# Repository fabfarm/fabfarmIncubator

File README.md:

# Fabfarm Egg Incubator

This is the code repository for the Fabfarm Egg Incubator, a project for controlling and monitoring the temperature, humidity, and egg tray position inside an egg incubator.

## Features

- Temperature control using a relay
- Humidity control using a vent servo
- Egg tray rotation using a tray servo
- Sensor data display on a TFT screen
- Web interface for configuration and data visualization
- Data logging to SPIFFS
- PID control for temperature and humidity

## Hardware Requirements

- ESP32 microcontroller
- BME280 temperature, humidity and pressure sensor
- Relay module for temperature control
- Servo motor for vent control (humidity)
- Servo motor for tray rotation
- TFT display (ILI9341 based)

## Software Dependencies

- Arduino IDE
- Adafruit BME280 library
- ESP32Servo library
- TFT_eSPI library
- ESPAsyncWebServer library
- WiFiManager library
- FS.h, SPIFFS.h, and SPI.h libraries (built-in)
- PID_v1 library

## Getting Started

1. Clone this repository to your local machine.
2. Open the project folder ./firmware using platformio.
3. Platformio will install the required libraries mentioned in the Software Dependencies section.
4. Connect the hardware components as described in the Hardware Requirements section.
5. Upload the code to the ESP32 microcontroller.
6. In first time connect to the "AutoConnectAP" Wi-Fi network and configure the Wi-Fi settings.
7. Access the web interface by navigating to the IP address displayed on the TFT screen.
8. Configure temperature, humidity, and servo settings using the web interface.
9. Monitor the incubator data on the web interface and TFT screen.

### React frontend

#### General Setup:

0. you must have node, npm or a comparable package manager installed. (node >18)
1. path to the `./firmware/client` folder
2. run `npm install` to locally install your dependencies for the project
3. add a `.env` file by copying the .env.example file and replacing the values with the IP produced by the chip when it is setting up. (This will most likely be a dynamic IP so it is important to check if this has changed with every setup.)

#### Developing

The react frontend lives as its own project in the `./firmware/client` folder.

We can host the development server

#### Building

In order to build the react frontend files you must have node and npm or a comparable package manager installed.

The frontend files are built, compressed and placed in the ESP32 filesystem.

To do this, path to `./firmware/client` and run `npm run build`.

After this you can flash the chip and it'll have the latest version of the frontend available to you.

## Functionality Overview

- The incubator monitors and controls temperature and humidity using a BME280 sensor and a relay and servo motor, respectively.
- The egg tray position is controlled by a servo motor, which rotates the tray at regular intervals.
- Sensor data is displayed on the TFT screen and logged to the ESP32's SPIFFS memory.
- A web interface is provided for configuring temperature, humidity, and servo settings, as well as for visualizing logged data.
- The system can be paused or resumed using the web interface.

## Contributing

Feel free to fork this repository and submit pull requests for bug fixes, improvements, or new features. Please ensure that your code follows the existing style and structure.

## License

This project is licensed under the MIT License. See the [LICENSE](LICENSE) file for more information.

## Acknowledgements

This project was written by Lucio.
The react frontend was built by @NoHara42

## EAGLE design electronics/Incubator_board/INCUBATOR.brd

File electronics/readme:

placeholder for electronics files

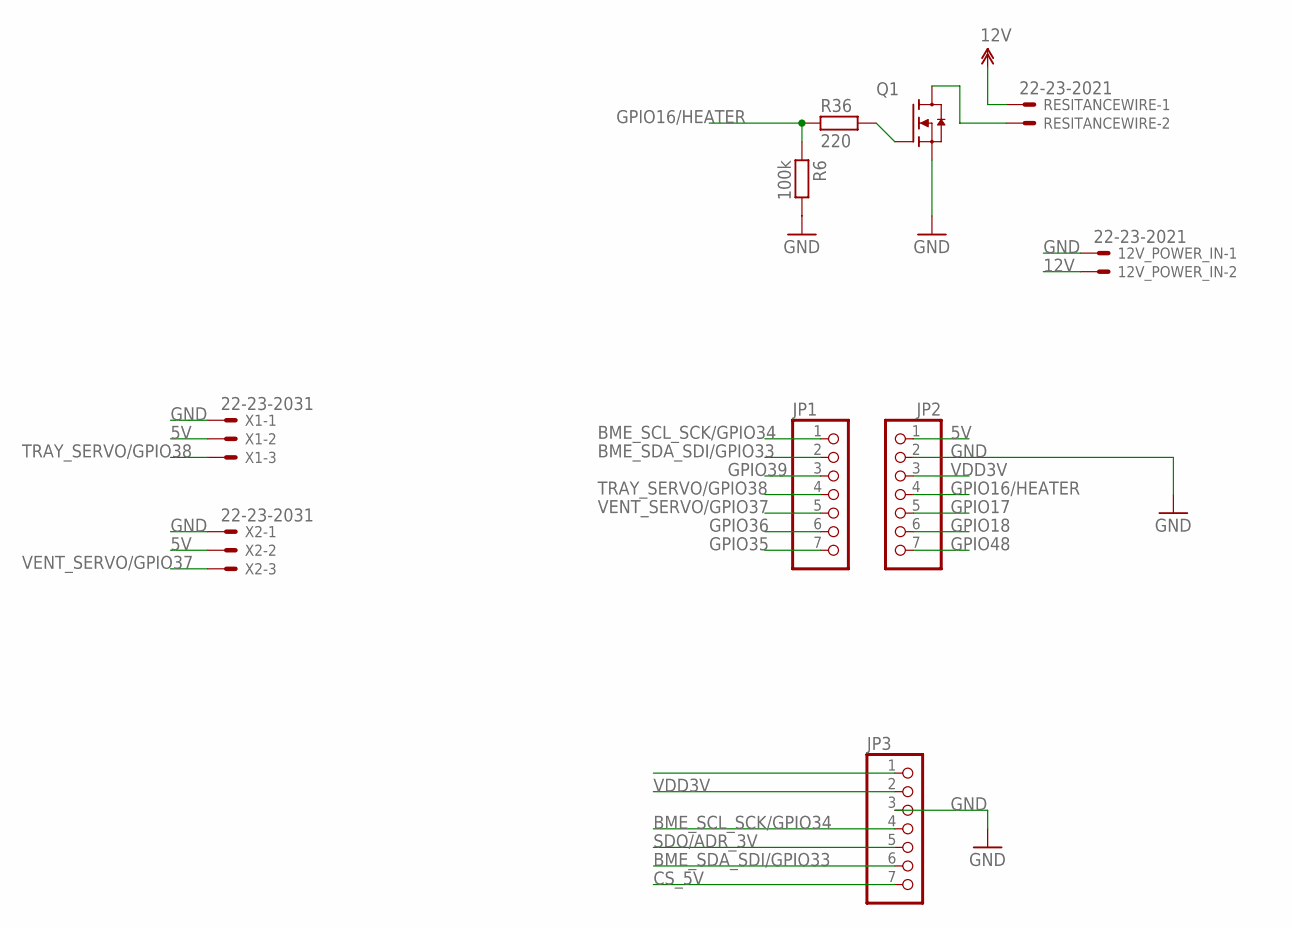
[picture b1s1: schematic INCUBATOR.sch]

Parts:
12V_POWER_IN: 22-23-2021
JP1, JP2: PINHD-1X7; 1X07
JP3: HEADER-1X770MIL; 1X07_ROUND_70
Q1: RFP30N06LE; TO92127P520H700-3
R6: 100k; RESC2012X70N
R36: 220; RESC2012X70N
RESITANCEWIRE: 22-23-2021
X1, X2: 22-23-2031

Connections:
5V: JP2.1, X1.2, X2.2
12V: 12V_POWER_IN.2, RESITANCEWIRE.1
BME_SCL_SCK/GPIO34: JP1.1, JP3.4
BME_SDA_SDI/GPIO33: JP1.2, JP3.6
CS_5V: JP3.7
GND: 12V_POWER_IN.1, JP2.2, JP3.3, Q1.S (SOURCE), R6.2, X1.1, X2.1
GPIO16/HEATER: JP2.4, R6.1, R36.1
GPIO17: JP2.5
GPIO18: JP2.6
GPIO35: JP1.7
GPIO36: JP1.6
GPIO39: JP1.3
GPIO48: JP2.7
HOTEND-GND: Q1.D (DRAIN), RESITANCEWIRE.2
unnamed: Q1.G (GATE), R36.2
SDO/ADR_3V: JP3.5
TRAY_SERVO/GPIO38: JP1.4, X1.3
VDD3V: JP2.3, JP3.2
VENT_SERVO/GPIO37: JP1.5, X2.3

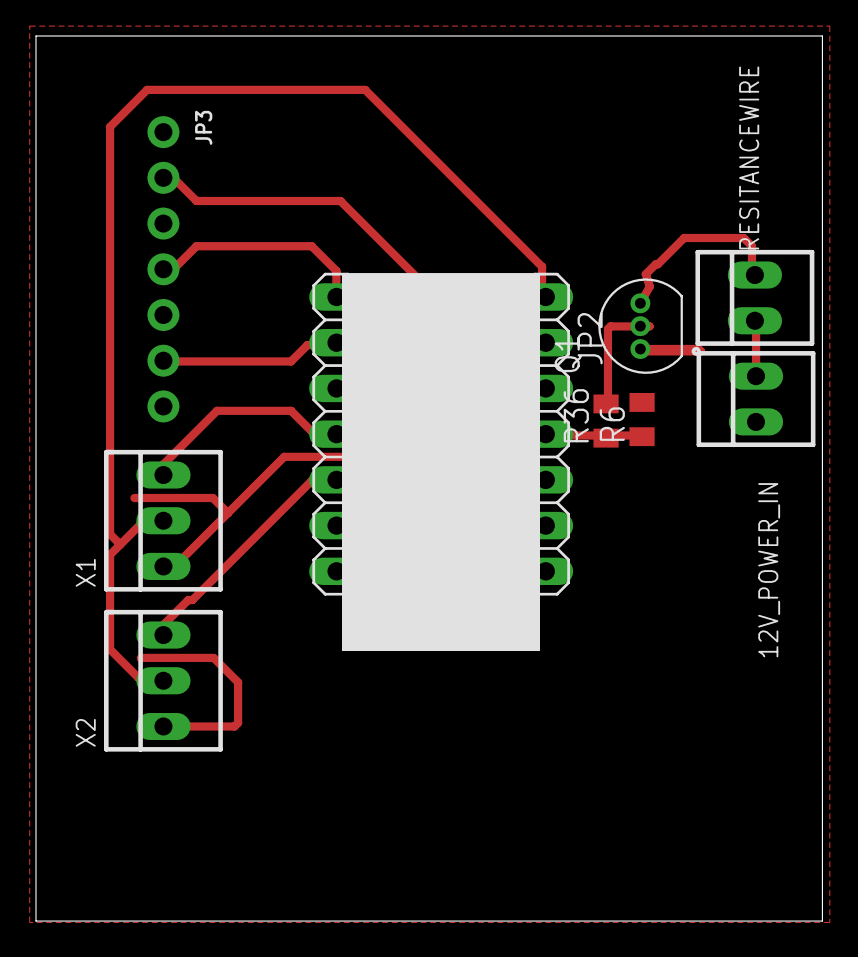
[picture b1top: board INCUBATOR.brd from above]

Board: 2 copper layers, 43.7 x 49.2 mm, 10 parts (0 on the bottom side), 11 nets.

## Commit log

2023-04-18 many changes to track
2023-04-19 added one decimal to temperatures
2023-04-21 improving layout
2023-04-24 added PID optimized code
2023-04-24 clean up
2023-04-24 many stuff
2023-04-24 bug fix
2023-04-25 new names for functions and variables
2023-04-30 Refactor: Remove hard-coded PID settings and move them to separate files Cleanup: Remove unnecessary files and improve PID configuration
2023-04-30 Reduce code size: Add ternary operator to function and implement it where necessary
2023-04-30 fix bug from last commit
2023-04-30 Refactoring code for improved readability and efficiency by reducing character count and simplifying logic
2023-04-30 fixed bug where the function where calling itself
2023-05-02 html now shows the current settings
2023-05-02 changes in html formating
2023-05-02 reducing code size
2023-05-03 cleanup
2023-05-03 changes in the readme
2023-05-04 simplified directory tree
2023-05-04 created a placeholder for the future electronics files and the cad files
2023-05-05 added notosans font
2023-05-05 moved Documentation folder to root
2023-05-05 added pcb
2023-05-08 add unix-friendly alternative shell script for development
2023-05-10 fix errors in unix alt flash script
2023-05-10 add comments for prereq steps
2023-05-10 changes in the board
2023-05-11 init preact project
2023-05-11 board updates
2023-05-11 add .clang-format file for unified formating
2023-05-11 restructure client folder
2023-05-11 removed PID deumbed down to a working version until sorted problems
2023-05-12 add .env to .gitignore
2023-05-12 temperature control without PID working added Elegant OTA
2023-05-12 gitignore additions
2023-05-15 add dependencies and fix comitted conflict markers
2023-05-15 fix tailwind config and add base styles
2023-05-15 add base template with mock data
2023-05-15 Refactor: Split code into distinct functionalities for better maintenance
    This commit divides the existing codebase into distinct and self-contained functionalities. This reorganization significantly improves the code's readability, maintainability, and potential for furth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
    No functionality has been added or removed in this commit; the focus was purely on restructuring the code for better maintenance.
2023-05-16 Refactor DisplayManager.cpp for better readability and maintenance
    This commit includes several improvements to the DisplayManager.cpp file:
    1. Extracted repeated code in updateTFTDisplay into a new function, updateLineIfChanged, to reduce code duplication and improve readability.
    2. Introduced a function, displayTargetValue, to handle displaying of target values, removing repeated code.
    3. Replaced magic numbers with named constants for better code clarity and ease of maintenance.
    4. Added comments for clarity.
    These changes should make the code easier to understand, modify, and maintain in the future.
2023-05-16 add dependencies and adapt scrips
2023-05-16 add env typing
2023-05-16 refactor app.tsx and add react-query
2023-05-16 add sidenav controls
2023-05-16 add build files
2023-05-16 extract endpoints to pure atoms
2023-05-16 fix misnaming
2023-05-18 remove whitespace
2023-05-18 adapt formatting config
2023-05-18 correct order of .sh script to stop error
2023-05-18 format and add readFile function to FileManager
2023-05-18 format main.cpp
2023-05-18 adapt package.json scripts and add build dep
2023-05-18 adapt build script
2023-05-18 decrease sampling speed via millis and seperate data to different .csv files
2023-05-18 Bump certifi from 2020.12.5 to 2022.12.7 in /firmware/lib/lvgl/docs
    Bumps [certifi](https://github.com/certifi/python-certifi) from 2020.12.5 to 2022.12.7.
    - [Commits](https://github.com/certifi/python-certifi/compare/2020.12.05...2022.12.07)
    ---
    updated-dependencies:
    - dependency-name: certifi
    dependency-type: direct:production
2023-05-18 Implement PID control for temperature and humidity
    - Added PID control functionality for both temperature and humidity
    - Declared necessary variables for PID control operation
    - Imported required libraries for PID control
    This implementation uses the PID Arduino library for controlling the temperature and humidity of a specific system. Each control loop has its corresponding input, output, setpoint, and tuning paramet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
2023-05-19 forgot some stuff for the PID
2023-05-19 added missing loadSettings parameters for the PID setings display.
2023-05-19 add ArduinoJson as platformio depedency
2023-05-19 correct by swapping x and y and increase sampling interval
2023-05-19 add fetchData handling via csv extraction and json obj building
2023-05-19 add serving of bundled assets
2023-05-19 add CORS headers
2023-05-19 Implement Inverted TTL Logic Where ON Represents LOW and Add File Reading Functionality on Root Handle Invocation
2023-05-19 extract endpoints into irreducible atoms and their handlers
2023-05-19 build files
2023-05-19 add dep
2023-05-19 adapt chart configs
2023-05-19 add live data :)
2023-05-19 add barebones.html file as fallback
2023-05-20 resolving merge conflicts
2023-05-20 fix .assets/barebones.html after the merge
2023-05-21 trying to fix merge problems
2023-05-21 add network reqs for other sidenav controls
2023-05-21 fix broken header import and format wifimanager
2023-05-21 format and fix status not toggling
2023-05-21 formatting with Microsoft C\C++ formatter
2023-05-21 formatting
2023-05-21 add script to atach USB to WSL & windows shortcut
2023-05-22 add readme and remove unused dependency
2023-05-22 fix build issue
2023-05-22 fix status reqest bug and give requests their proper semantic label
2023-05-22 fix gitignore and organise frontend sidenav
2023-05-22 build assets
2023-05-23 Bump requests from 2.25.1 to 2.31.0 in /firmware/lib/lvgl/docs
    Bumps [requests](https://github.com/psf/requests) from 2.25.1 to 2.31.0.
    - [Release notes](https://github.com/psf/requests/releases)
    - [Changelog](https://github.com/psf/requests/blob/main/HISTORY.md)
    - [Commits](https://github.com/psf/requests/compare/v2.25.1...v2.31.0)
    ---
    updated-dependencies:
2023-05-24 use TFT library by Platformio instead of local
2023-05-24 remove unused libraries
2023-05-27 siplify code prepare to rewrite all TFT functions
2023-05-27 simplify to barebones, version remove react
2023-05-27 fix fetch data
2023-05-27 Change data source to data.txt for barebones.
2023-05-27 fix data.txt and mosfet control
2023-05-27 remove unused variables
2023-05-27 print status on monitor only when changed
2023-05-27 add variable timeIntervalToSaveData
2023-05-27 remove redundant debugMessage
2023-05-27 initialize TFT and configure TFT on platformio.ini
2023-05-28 correct driver for the tft display on platformio
2023-05-28 show Temperature, Humidity and Preassure on TFT
2023-05-28 fix humidity display, set variable for tft refresh
2023-05-28 print set humidity and temperature
2023-05-28 fix variable
2023-05-28 create only firmware script, change script name
2023-05-28 fix run incubator function
2023-05-28 fix print ghost on tftdisplay when numbers change
2023-05-28 fix bug
2023-05-29 comment some things
2023-05-31 vscode colors
2023-08-03 Bump vite from 4.3.5 to 4.3.9 in /firmware/client
    Bumps [vite](https://github.com/vitejs/vite/tree/HEAD/packages/vite) from 4.3.5 to 4.3.9.
    - [Release notes](https://github.com/vitejs/vite/releases)
    - [Changelog](https://github.com/vitejs/vite/blob/main/packages/vite/CHANGELOG.md)
    - [Commits](https://github.com/vitejs/vite/commits/v4.3.9/packages/vite)
    ---
    updated-dependencies:
2023-12-06 Bump postcss from 8.4.23 to 8.4.31 in /firmware/client
    Bumps [postcss](https://github.com/postcss/postcss) from 8.4.23 to 8.4.31.
    - [Release notes](https://github.com/postcss/postcss/releases)
    - [Changelog](https://github.com/postcss/postcss/blob/main/CHANGELOG.md)
    - [Commits](https://github.com/postcss/postcss/compare/8.4.23...8.4.31)
    ---
    updated-dependencies:
2023-12-06 Bump @babel/traverse from 7.21.5 to 7.23.5 in /firmware/client
    Bumps [@babel/traverse](https://github.com/babel/babel/tree/HEAD/packages/babel-traverse) from 7.21.5 to 7.23.5.
    - [Release notes](https://github.com/babel/babel/releases)
    - [Changelog](https://github.com/babel/babel/blob/main/CHANGELOG.md)
    - [Commits](https://github.com/babel/babel/commits/v7.23.5/packages/babel-traverse)
    ---
    updated-dependencies:
2024-01-20 Bump vite from 4.3.9 to 4.5.2 in /firmware/client
    Bumps [vite](https://github.com/vitejs/vite/tree/HEAD/packages/vite) from 4.3.9 to 4.5.2.
    - [Release notes](https://github.com/vitejs/vite/releases)
    - [Changelog](https://github.com/vitejs/vite/blob/v4.5.2/packages/vite/CHANGELOG.md)
    - [Commits](https://github.com/vitejs/vite/commits/v4.5.2/packages/vite)
    ---
    updated-dependencies:
2024-04-03 Bump vite from 4.3.9 to 4.5.3 in /firmware/client
    Bumps [vite](https://github.com/vitejs/vite/tree/HEAD/packages/vite) from 4.3.9 to 4.5.3.
    - [Release notes](https://github.com/vitejs/vite/releases)
    - [Changelog](https://github.com/vitejs/vite/blob/v4.5.3/packages/vite/CHANGELOG.md)
    - [Commits](https://github.com/vitejs/vite/commits/v4.5.3/packages/vite)
    ---
    updated-dependencies:
2024-04-17 gitignore
2024-04-17 modify gitignore
